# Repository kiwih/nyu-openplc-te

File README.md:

# NYU OpenPLC Trojan Edition (TE)

This repository contains NYU's implementation of the OpenPLC hardware. 
Several important modifications are included, notably, a socket for a second
microcontroller (a Raspberry Pi Pico) which can act as a 'Hardware Trojan'.
Different Hardware Trojan capabilities can be enabled and disabled depending on the configuration of a number of jumpers located around the PCB.

There are a small number of known issues with the v0.1 board. 
These include the usage of a now-obsolete accelerometer, and poor component
choice for on-board power measurement circuitry.

These will be remedied for version 0.2 of this work.

This PCB was used in the paper,
"Detecting Hardware Trojans in PCBs Using Side Channel Loopbacks"
by Hammond Pearce, Virinchi Roy Surabhi, Prashanth Krishnamurthy,
Joshua Trujillo, Ramesh Karri, and Farshad Khorrami.
Published in IEEE TVLSI, 2022.

## Repository contents

`/final-outputs-v0.1` - this includes the schematic files, BOM CSVs, PDF layout files, and final production gerbers of the PCB manufactured for use in the paper.

`/kicad-files-v0.1` - this contains the KiCAD project used to make the project.

## New versions of the PCB

Newer versions (v0.2 and above) are currently under active development and will be released through this repository upon validation.

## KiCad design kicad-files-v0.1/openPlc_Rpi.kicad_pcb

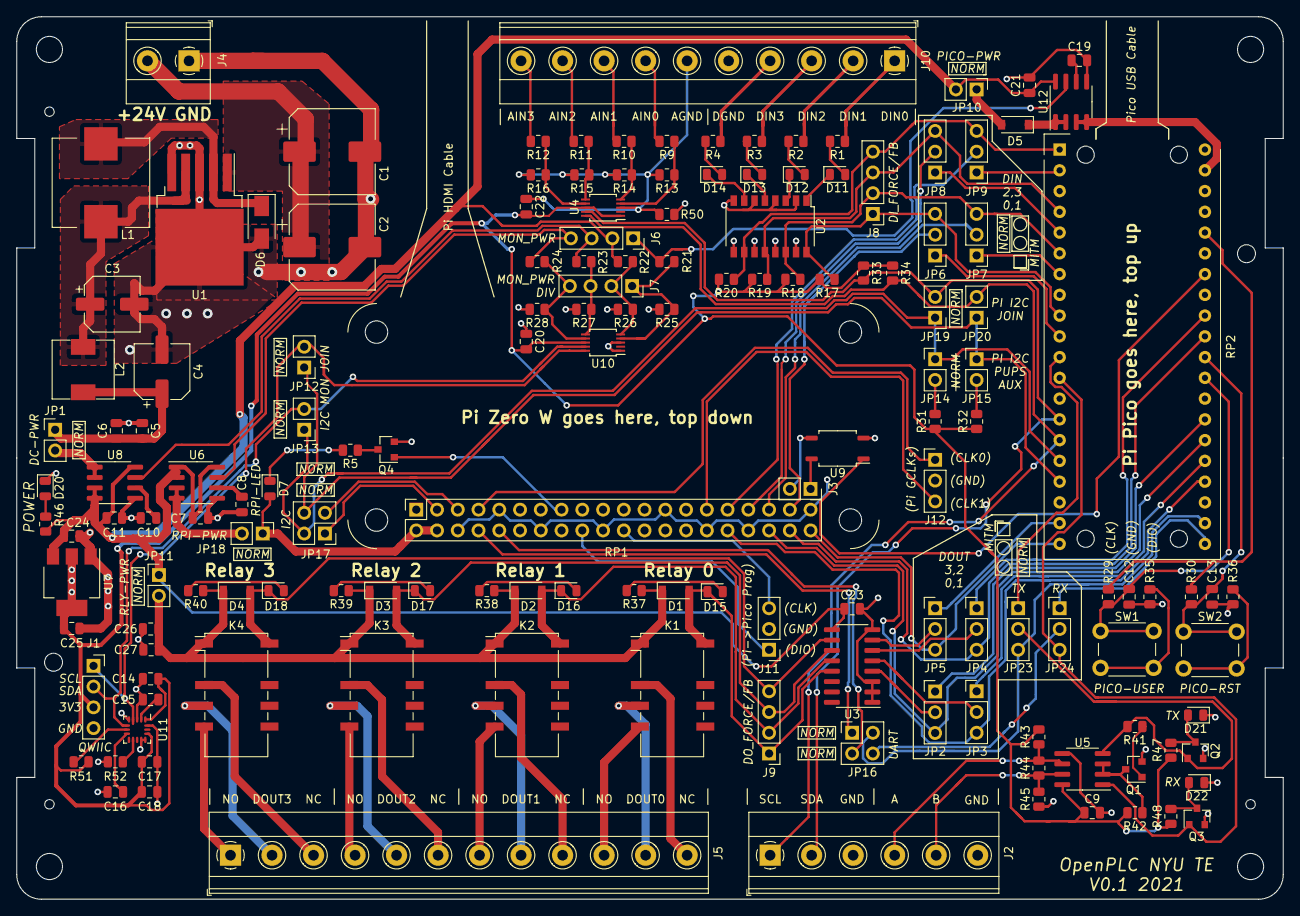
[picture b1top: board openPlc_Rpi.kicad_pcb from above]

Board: 2 copper layers, 155.0 x 108.0 mm, 162 parts (0 on the bottom side), 133 nets.

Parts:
C1, C2: 220uF; CP_Elec_10x10
C3, C4: 180uF; CP_Elec_6.3x7.7
C5, C26: 4.7uF; C_0805_2012Metric
C6, C7, C9, C11, C12, C13, C14, C15, C16, C17, C21, C27: 100nF; C_0805_2012Metric
C8, C10, C19: 1nF; C_0805_2012Metric
C18: 4.7uf; C_0805_2012Metric
C20, C22: 100n; C_0805_2012Metric
C23: 100nf; C_0805_2012Metric
C24, C25: 22uf; C_0805_2012Metric
D1, D2, D3, D4, D5: B5819W; D_SOD-123
D6: SS54; D_SMA
D7, D11, D12, D13, D14, D15, D16, D17, D18, D20, D21, D22: LED; LED_0805_2012Metric
FID1, FID2, FID3: Fiducial; jlcpcb-fiducial
H1, H2: MountingHole; MountingHole_2.2mm_M2
H3, H4, H5, H6: MountingHole; MountingHole_3.2mm_M3
J1, J6, J7: Conn_01x04; PinSocket_1x04_P2.54mm_Vertical
J2: Screw_Terminal_01x06; TerminalBlock_Phoenix_MKDS-1,5-6-5.08_1x06_P5.08mm_Horizont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
J3: Conn_01x02; PinSocket_1x02_P2.54mm_Vertical
J4: Screw_Terminal_01x02; TerminalBlock_Phoenix_MKDS-1,5-2-5.08_1x02_P5.08mm_Horizont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
J5: Screw_Terminal_01x12; TerminalBlock_Phoenix_MKDS-1,5-12-5.08_1x12_P5.08mm_Horizon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
J8, J9: Conn_01x04; PinHeader_1x04_P2.54mm_Vertical
J10: Conn_01x10; TerminalBlock_Phoenix_MKDS-1,5-10-5.08_1x10_P5.08mm_Horizon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
J11, J12: Conn_01x03; PinHeader_1x03_P2.54mm_Vertical
JP1, JP10, JP11, JP12, JP13, JP14, JP15, JP18, JP19, JP20: Jumper; PinHeader_1x02_P2.54mm_Vertical
JP2, JP3, JP4, JP5, JP6, JP7, JP8, JP9, JP23, JP24: Jumper_3_Bridged12; PinHeader_1x03_P2.54mm_Vertical
JP16, JP17: Conn_02x02_Odd_Even; PinHeader_2x02_P2.54mm_Vertical
K1, K2, K3, K4: G6S-2; Relay_DPDT_Omron_G6S-2F
L1: 68uH; L_10x11.5mm_H4mm
L2: 3.3uH; L_7.1x6.6_H3
Q1, Q2, Q3, Q4: 2N7002; SOT-23
R1, R2, R3, R4: 1k; R_0805_2012Metric
R5, R37, R38, R39, R40, R44, R46, R47, R48: 120R; R_0805_2012Metric
R9, R10, R11, R12: 100k; R_0805_2012Metric
R13, R14, R15, R16: 16k; R_0805_2012Metric
R17, R18, R19, R20, R21, R22, R23, R24, R41, R42: 10k; R_0805_2012Metric
R25: 20k; R_0805_2012Metric
R26: 20K; R_0805_2012Metric
R27, R28: 5K; R_0805_2012Metric
R29, R30, R31, R32, R33, R34, R51, R52: 10K; R_0805_2012Metric
R35, R36: 100R; R_0805_2012Metric
R43, R45: DNF; R_0805_2012Metric
R50: 0; R_0805_2012Metric
RP1: Raspberry_Pi_2_3; RPiZero-Hat
RP2: raspberrypi-pico-module
SW1, SW2: SW_Push; SW_PUSH_6mm
U1: LM2596S-5; TO-263-5_TabPin3
U2: LTV-247; SOP-16_4.4x10.4mm_P1.27mm
U3: ULN2003A; SOIC-16_3.9x9.9mm_P1.27mm
U4, U10: ADS1115IDGS; TSSOP-10_3x3mm_P0.5mm
U5: SP3485EN; SOIC-8_3.9x4.9mm_P1.27mm
U6, U8, U12: ACS712xLCTR-05B; SOIC-8_3.9x4.9mm_P1.27mm
U7: AMS1117-3.3; SOT-223-3_TabPin2
U9: EL357N; SOP-4_4.1x4.4mm_P2.54mm
U11: FXOS8700CQ; QFN-16_5.3.5.3_3x3_Pitch0.5mm

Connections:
+3V3: C9.1, C14.1, C17.1, C18.1, C20.2, C22.2, C25.1, J1.3, R17.1, R18.1, R19.1, R20.1, R31.1, R32.1, R33.1, R34.1, R42.2, R43.2, R47.1, R48.1, R51.2, U4.1, U4.8, U5.8, U7.2, U10.8, U11.1, U11.14
+5V: C7.1, C11.1, C21.1, C23.1, C24.1, J6.2, JP10.2, JP11.1, R22.2, R46.1, U3.9, U6.1, U6.2, U6.8, U7.3, U8.3, U8.4, U8.8, U12.8
+24V: C1.1, C2.1, J4.2, U1.1
/1: J5.10, K1.5
/2: J5.11, K1.4
/3: J5.12, K1.3
/3V3_5V: J7.2, R22.1, R26.1, U10.5
/3V3_I_5V: J7.3, R23.1, R27.1, U10.6
/3V3_I_5V_PI: J7.4, R24.1, R28.1, U10.7
/3V3_I_5V_PICO: J7.1, R21.1, R25.1, U10.4
/4: J5.7, K2.5
/5: J5.8, K2.4
/5V_IN: JP1.2, U8.1, U8.2
/5V_PI: D7.2, JP18.1, RP1.2, RP1.4
/5V_PICO: RP2.39, U12.3, U12.4
/5V_PICO_IN: D5.1, U12.1, U12.2
/5V_RELAYS: C26.1, C27.1, D1.1, D2.1, D3.1, D4.1, JP11.2, K1.1, K2.1, K3.1, K4.1, R37.1, R38.1, R39.1, R40.1
/6: J5.9, K2.3
/7: J5.4, K3.5
/8: J5.5, K3.4
/9: J5.6, K3.3
/10: J5.1, K4.5
/11: J5.2, K4.4
/12: J5.3, K4.3
/A: J2.4, R43.1, R44.2, U5.6
/AGND: C22.1, J10.6, R13.2, R14.2, R15.2, R16.2, R50.1, U4.3
/AIN0: J10.7, R9.2
/AIN1: J10.8, R10.2
/AIN2: J10.9, R11.2
/AIN3: J10.10, R12.2
/B: J2.5, R44.1, R45.2, U5.7
/CLK0: J12.1, RP1.7
/CLK1: J12.3, RP1.29
/DIN0: J10.1, R1.2
/DIN1: J10.2, R2.2
/DIN2: J10.3, R3.2
/DIN3: J10.4, R4.2
/DI_0: J8.1, JP6.3, R17.2, RP2.9, U2.16
/DI_1: J8.2, JP7.3, R18.2, RP2.6, U2.14
/DI_2: J8.3, JP8.3, R19.2, RP2.4, U2.12
/DI_3: J8.4, JP9.3, R20.2, RP2.1, U2.10
/DO0_RELAY: D1.2, D15.1, J9.1, K1.12, U3.13
/DO1_RELAY: D2.2, D16.1, J9.2, K2.12, U3.12
/DO2_RELAY: D3.2, D17.1, J9.3, K3.12, U3.11
/DO3_RELAY: D4.2, D18.1, J9.4, K4.12, U3.10
/I_5V: J6.3, R23.2, U8.7
/I_5V_PI: J6.4, R24.2, U6.7
/I_5V_PICO: J6.1, R21.2, U12.7
/MON_I2C_SCL: J1.1, JP12.2, U10.10, U11.4
/MON_I2C_SDA: J1.2, JP13.2, U10.9, U11.6
/PI_RUN: RP2.34, U9.1
/PI_RUN_RAW: J3.1, U9.4
/PI_RXD: JP16.4, JP24.2
/PI_RX_RAW: JP16.3, RP1.10
/PI_SCL_RAW: JP17.3, RP1.5
/PI_SDA_RAW: JP17.1, RP1.3
/PI_TXD: JP16.2, JP23.3, RP2.22
/PI_TX_RAW: JP16.1, RP1.8
/RUN: C13.2, R30.2, RP2.30, SW2.1
/RXD: JP24.3, Q3.1, RP2.12, U5.1
/ST_3V3_OUT: R29.1, R30.1, RP2.36
/ST_ENV_DO_0: JP2.1, RP2.27
/ST_ENV_DO_1: JP3.1, RP2.25
/ST_ENV_DO_2: JP4.1, RP2.32
/ST_ENV_DO_3: JP5.1, RP2.19
/ST_ENV_TXD: JP23.1, RP2.11
/ST_I2C_SCL: J2.1, JP20.2, R34.2, RP2.15, U4.10
/ST_I2C_SDA: J2.2, JP19.2, R33.2, RP2.14, U4.9
/ST_PI_DI_0: JP6.1, RP2.10
/ST_PI_DI_1: JP7.1, RP2.7
/ST_PI_DI_2: JP8.1, RP2.5
/ST_PI_DI_3: JP9.1, RP2.2
/ST_PI_TXD: JP24.1, RP2.21
/SWCLK: J11.3, RP1.22
/SWDIO: J11.1, RP1.18
/TROJ_PB: C12.2, R29.2, RP2.29, SW1.1
/TXD: JP23.2, Q2.1, R41.2, U5.4
DO_0: JP2.2, U3.4
DO_1: JP3.2, U3.5
DO_2: JP4.2, U3.6
DO_3: JP5.2, U3.7
GND: C1.2, C2.2, C3.2, C4.2, C5.2, C6.2, C7.2, C8.2, C9.2, C10.2, C11.2, C12.1, C13.1, C14.2, C15.2, C16.2, C17.2, C18.2, C19.2, C20.1, C21.2, C23.2, C24.2, C25.2, C26.2, C27.2, D6.2, D20.1, D21.1, D22.1, J1.4, J2.3, J2.6, J4.1, J10.5, J11.2, J12.2, Q1.2, Q2.2, Q3.2, Q4.2, R25.2, R26.2, R27.2, R28.2, R35.2, R36.2, R45.1, R50.2, R52.2, RP1.6, RP1.9, RP1.14, RP1.20, RP1.25, RP1.30, RP1.34, RP1.39, RP2.3, RP2.8, RP2.13, RP2.18, RP2.23, RP2.28, RP2.33, RP2.38, U1.3, U1.5, U2.2, U2.4, U2.6, U2.8, U2.9, U2.11, U2.13, U2.15, U3.1, U3.2, U3.3, U3.8, U5.5, U6.5, U7.1, U8.5, U9.2, U10.1, U10.3, U11.3, U11.5, U11.12, U11.13, U11.16, U12.5
LED: Q4.1, RP1.15
unnamed: C3.1, L1.2, L2.1, U1.4
unnamed: C4.1, C5.1, C6.1, JP1.1, L2.2
unnamed: C8.1, U6.6
unnamed: C10.1, U8.6
unnamed: C15.1, U11.2
unnamed: C16.1, U11.8
unnamed: C19.1, U12.6
unnamed: D5.2, JP10.1
unnamed: D6.1, L1.1, U1.2
unnamed: D7.1, R5.1
unnamed: D11.1, U2.1
unnamed: D11.2, R1.1
unnamed: D12.1, U2.3
unnamed: D12.2, R2.1
unnamed: D13.1, U2.5
unnamed: D13.2, R3.1
unnamed: D14.1, U2.7
unnamed: D14.2, R4.1
unnamed: D15.2, R37.2
unnamed: D16.2, R38.2
unnamed: D17.2, R39.2
unnamed: D18.2, R40.2
unnamed: D20.2, R46.2
unnamed: D21.2, Q2.3, R47.2
unnamed: D22.2, Q3.3, R48.2
unnamed: J3.2, U9.3
unnamed: JP14.2, R31.2
unnamed: JP15.2, R32.2
unnamed: JP18.2, U6.3, U6.4
unnamed: Q1.1, R41.1
unnamed: Q1.3, R42.1, U5.2, U5.3
unnamed: Q4.3, R5.2
unnamed: R10.1, R14.1, U4.5
unnamed: R11.1, R15.1, U4.6
unnamed: R12.1, R16.1, U4.7
unnamed: R9.1, R13.1, U4.4
unnamed: R35.1, SW1.2
unnamed: R36.1, SW2.2
unnamed: R51.1, U11.7
unnamed: R52.1, U11.10
PI_DI_0: JP6.2, RP1.37
PI_DI_1: JP7.2, RP1.35
PI_DI_2: JP8.2, RP1.33
PI_DI_3: JP9.2, RP1.31
PI_DO_0: JP2.3, RP1.36, RP2.26
PI_DO_1: JP3.3, RP1.32, RP2.24
PI_DO_2: JP4.3, RP1.38, RP2.31
PI_DO_3: JP5.3, RP1.40, RP2.20
PI_I2C_SCL: JP12.1, JP15.1, JP17.4, JP20.1, RP2.17
PI_I2C_SDA: JP13.1, JP14.1, JP17.2, JP19.1, RP2.16

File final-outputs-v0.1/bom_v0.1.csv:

Designator,Comment,Footprint,Manufacturer,Vendor
C1,220uF,Capacitor_SMD:CP_Elec_10x10,,C134519
C2,220uF,Capacitor_SMD:CP_Elec_10x10,,C134519
C3,180uF,Capacitor_SMD:CP_Elec_6.3x7.7,,C413657
C4,180uF,Capacitor_SMD:CP_Elec_6.3x7.7,,C413657
C5,4.7uF,Capacitor_SMD:C_0805_2012Metric,,C1779
C6,100nF,Capacitor_SMD:C_0805_2012Metric,,C49678
C7,100nF,Capacitor_SMD:C_0805_2012Metric,,C49678
C8,1nF,Capacitor_SMD:C_0805_2012Metric,,C46653
C9,100nF,Capacitor_SMD:C_0805_2012Metric,,C49678
C10,1nF,Capacitor_SMD:C_0805_2012Metric,,C46653
C11,100nF,Capacitor_SMD:C_0805_2012Metric,,C49678
C12,100nF,Capacitor_SMD:C_0805_2012Metric,,C49678
C13,100nF,Capacitor_SMD:C_0805_2012Metric,,C49678
C14,100nF,Capacitor_SMD:C_0805_2012Metric,,C49678
C15,100nF,Capacitor_SMD:C_0805_2012Metric,,C49678
C16,100nF,Capacitor_SMD:C_0805_2012Metric,,C49678
C17,100nF,Capacitor_SMD:C_0805_2012Metric,,C49678
C18,4.7uf,Capacitor_SMD:C_0805_2012Metric,,C1779
C19,1nF,Capacitor_SMD:C_0805_2012Metric,,C46653
C20,100n,Capacitor_SMD:C_0805_2012Metric,,C49678
C21,100nF,Capacitor_SMD:C_0805_2012Metric,,C49678
C22,100n,Capacitor_SMD:C_0805_2012Metric,,C49678
C23,100nf,Capacitor_SMD:C_0805_2012Metric,,C49678
C24,22uf,Capacitor_SMD:C_0805_2012Metric,,C45783
C25,22uf,Capacitor_SMD:C_0805_2012Metric,,C45783
C26,4.7uF,Capacitor_SMD:C_0805_2012Metric,,C1779
C27,100nF,Capacitor_SMD:C_0805_2012Metric,,C49678
D1,B5819W,Diode_SMD:D_SOD-123,,C8598
D2,B5819W,Diode_SMD:D_SOD-123,,C8598
D3,B5819W,Diode_SMD:D_SOD-123,,C8598
D4,B5819W,Diode_SMD:D_SOD-123,,C8598
D5,B5819W,Diode_SMD:D_SOD-123,,C8598
D6,SS54,Diode_SMD:D_SMA,,C22452
D7,LED,LED_SMD:LED_0805_2012Metric,,C2297
D11,LED,LED_SMD:LED_0805_2012Metric,,C2297
D12,LED,LED_SMD:LED_0805_2012Metric,,C2297
D13,LED,LED_SMD:LED_0805_2012Metric,,C2297
D14,LED,LED_SMD:LED_0805_2012Metric,,C2297
D15,LED,LED_SMD:LED_0805_2012Metric,,C2297
D16,LED,LED_SMD:LED_0805_2012Metric,,C2297
D17,LED,LED_SMD:LED_0805_2012Metric,,C2297
D18,LED,LED_SMD:LED_0805_2012Metric,,C2297
D20,LED,LED_SMD:LED_0805_2012Metric,,C2297
D21,LED,LED_SMD:LED_0805_2012Metric,,C2293
D22,LED,LED_SMD:LED_0805_2012Metric,,C2293
K1,G6S-2,Relay_SMD:Relay_DPDT_Omron_G6S-2F,,C397130
K2,G6S-2,Relay_SMD:Relay_DPDT_Omron_G6S-2F,,C397130
K3,G6S-2,Relay_SMD:Relay_DPDT_Omron_G6S-2F,,C397130
K4,G6S-2,Relay_SMD:Relay_DPDT_Omron_G6S-2F,,C397130
L1,68uH,kiwih_kicad:L_10x11.5mm_H4mm,,C497902
L2,3.3uH,kiwih_kicad:L_7.1x6.6_H3,,C207839
Q1,2N7002,Package_TO_SOT_SMD:SOT-23,,C8545
Q2,2N7002,Package_TO_SOT_SMD:SOT-23,,C8545
Q3,2N7002,Package_TO_SOT_SMD:SOT-23,,C8545
Q4,2N7002,Package_TO_SOT_SMD:SOT-23,,C8545
R1,1k,Resistor_SMD:R_0805_2012Metric,,C17513
R2,1k,Resistor_SMD:R_0805_2012Metric,,C17513
R3,1k,Resistor_SMD:R_0805_2012Metric,,C17513
R4,1k,Resistor_SMD:R_0805_2012Metric,,C17513
R5,120R,Resistor_SMD:R_0805_2012Metric,,C17437
R9,100k,Resistor_SMD:R_0805_2012Metric,,C17407
R10,100k,Resistor_SMD:R_0805_2012Metric,,C17407
R11,100k,Resistor_SMD:R_0805_2012Metric,,C17407
R12,100k,Resistor_SMD:R_0805_2012Metric,,C17407
R13,16k,Resistor_SMD:R_0805_2012Metric,,C17490
R14,16k,Resistor_SMD:R_0805_2012Metric,,C17490
R15,16k,Resistor_SMD:R_0805_2012Metric,,C17490
R16,16k,Resistor_SMD:R_0805_2012Metric,,C17490
R17,10k,Resistor_SMD:R_0805_2012Metric,,C17414
R18,10k,Resistor_SMD:R_0805_2012Metric,,C17414
R19,10k,Resistor_SMD:R_0805_2012Metric,,C17414
R20,10k,Resistor_SMD:R_0805_2012Metric,,C17414
R21,10k,Resistor_SMD:R_0805_2012Metric,,C17414
R22,10k,Resistor_SMD:R_0805_2012Metric,,C17414
R23,10k,Resistor_SMD:R_0805_2012Metric,,C17414
R24,10k,Resistor_SMD:R_0805_2012Metric,,C17414
R25,20k,Resistor_SMD:R_0805_2012Metric,,C4328
R26,20K,Resistor_SMD:R_0805_2012Metric,,C4328
R27,5K,Resistor_SMD:R_0805_2012Metric,,C4328
R28,5K,Resistor_SMD:R_0805_2012Metric,,C4328
R29,10K,Resistor_SMD:R_0805_2012Metric,,C17414
R30,10K,Resistor_SMD:R_0805_2012Metric,,C17414
R31,10K,Resistor_SMD:R_0805_2012Metric,,C17414
R32,10K,Resistor_SMD:R_0805_2012Metric,,C17414
R33,10K,Resistor_SMD:R_0805_2012Metric,,C17414
R34,10K,Resistor_SMD:R_0805_2012Metric,,C17414
R35,100R,Resistor_SMD:R_0805_2012Metric,,C17408
R36,100R,Resistor_SMD:R_0805_2012Metric,,C17408
R37,120R,Resistor_SMD:R_0805_2012Metric,,C17437
R38,120R,Resistor_SMD:R_0805_2012Metric,,C17437
R39,120R,Resistor_SMD:R_0805_2012Metric,,C17437
R40,120R,Resistor_SMD:R_0805_2012Metric,,C17437
R41,10k,Resistor_SMD:R_0805_2012Metric,,C17414
R42,10k,Resistor_SMD:R_0805_2012Metric,,C17414
R43,DNF,Resistor_SMD:R_0805_2012Metric,,
R44,120R,Resistor_SMD:R_0805_2012Metric,,C17437
R45,DNF,Resistor_SMD:R_0805_2012Metric,,
R46,120R,Resistor_SMD:R_0805_2012Metric,,C17437
R47,120R,Resistor_SMD:R_0805_2012Metric,,C17437
R48,120R,Resistor_SMD:R_0805_2012Metric,,C17437
R50,0,Resistor_SMD:R_0805_2012Metric,,C17477
R51,10K,Resistor_SMD:R_0805_2012Metric,,C17414
R52,10K,Resistor_SMD:R_0805_2012Metric,,C17414
U1,LM2596S-5,Package_TO_SOT_SMD:TO-263-5_TabPin3,,C10002
U2,LTV-247,Package_SO:SOP-16_4.4x10.4mm_P1.27mm,,C115451
U3,ULN2003A,Package_SO:SOIC-16_3.9x9.9mm_P1.27mm,,C7512
U4,ADS1115IDGS,Package_SO:TSSOP-10_3x3mm_P0.5mm,,C37593
U5,SP3485EN,Package_SO:SOIC-8_3.9x4.9mm_P1.27mm,,C8963
U6,ACS712xLCTR-05B,Package_SO:SOIC-8_3.9x4.9mm_P1.27mm,,C44471
U7,AMS1117-3.3,Package_TO_SOT_SMD:SOT-223-3_TabPin2,,C6186
U8,ACS712xLCTR-05B,Package_SO:SOIC-8_3.9x4.9mm_P1.27mm,,C44471
U9,EL357N,kiwih_kicad:SOP-4_4.1x4.4mm_P2.54mm,,C6649
U10,ADS1115IDGS,Package_SO:TSSOP-10_3x3mm_P0.5mm,,C37593
U11,FXOS8700CQ,kiwih_kicad:QFN-16_5.3.5.3_3x3_Pitch0.5mm,,C432308
U12,ACS712xLCTR-05B,Package_SO:SOIC-8_3.9x4.9mm_P1.27mm,,C44471

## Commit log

2022-04-18 v0.1 files
2022-04-18 Create LICENSE
2022-04-18 Update README to fix typos
